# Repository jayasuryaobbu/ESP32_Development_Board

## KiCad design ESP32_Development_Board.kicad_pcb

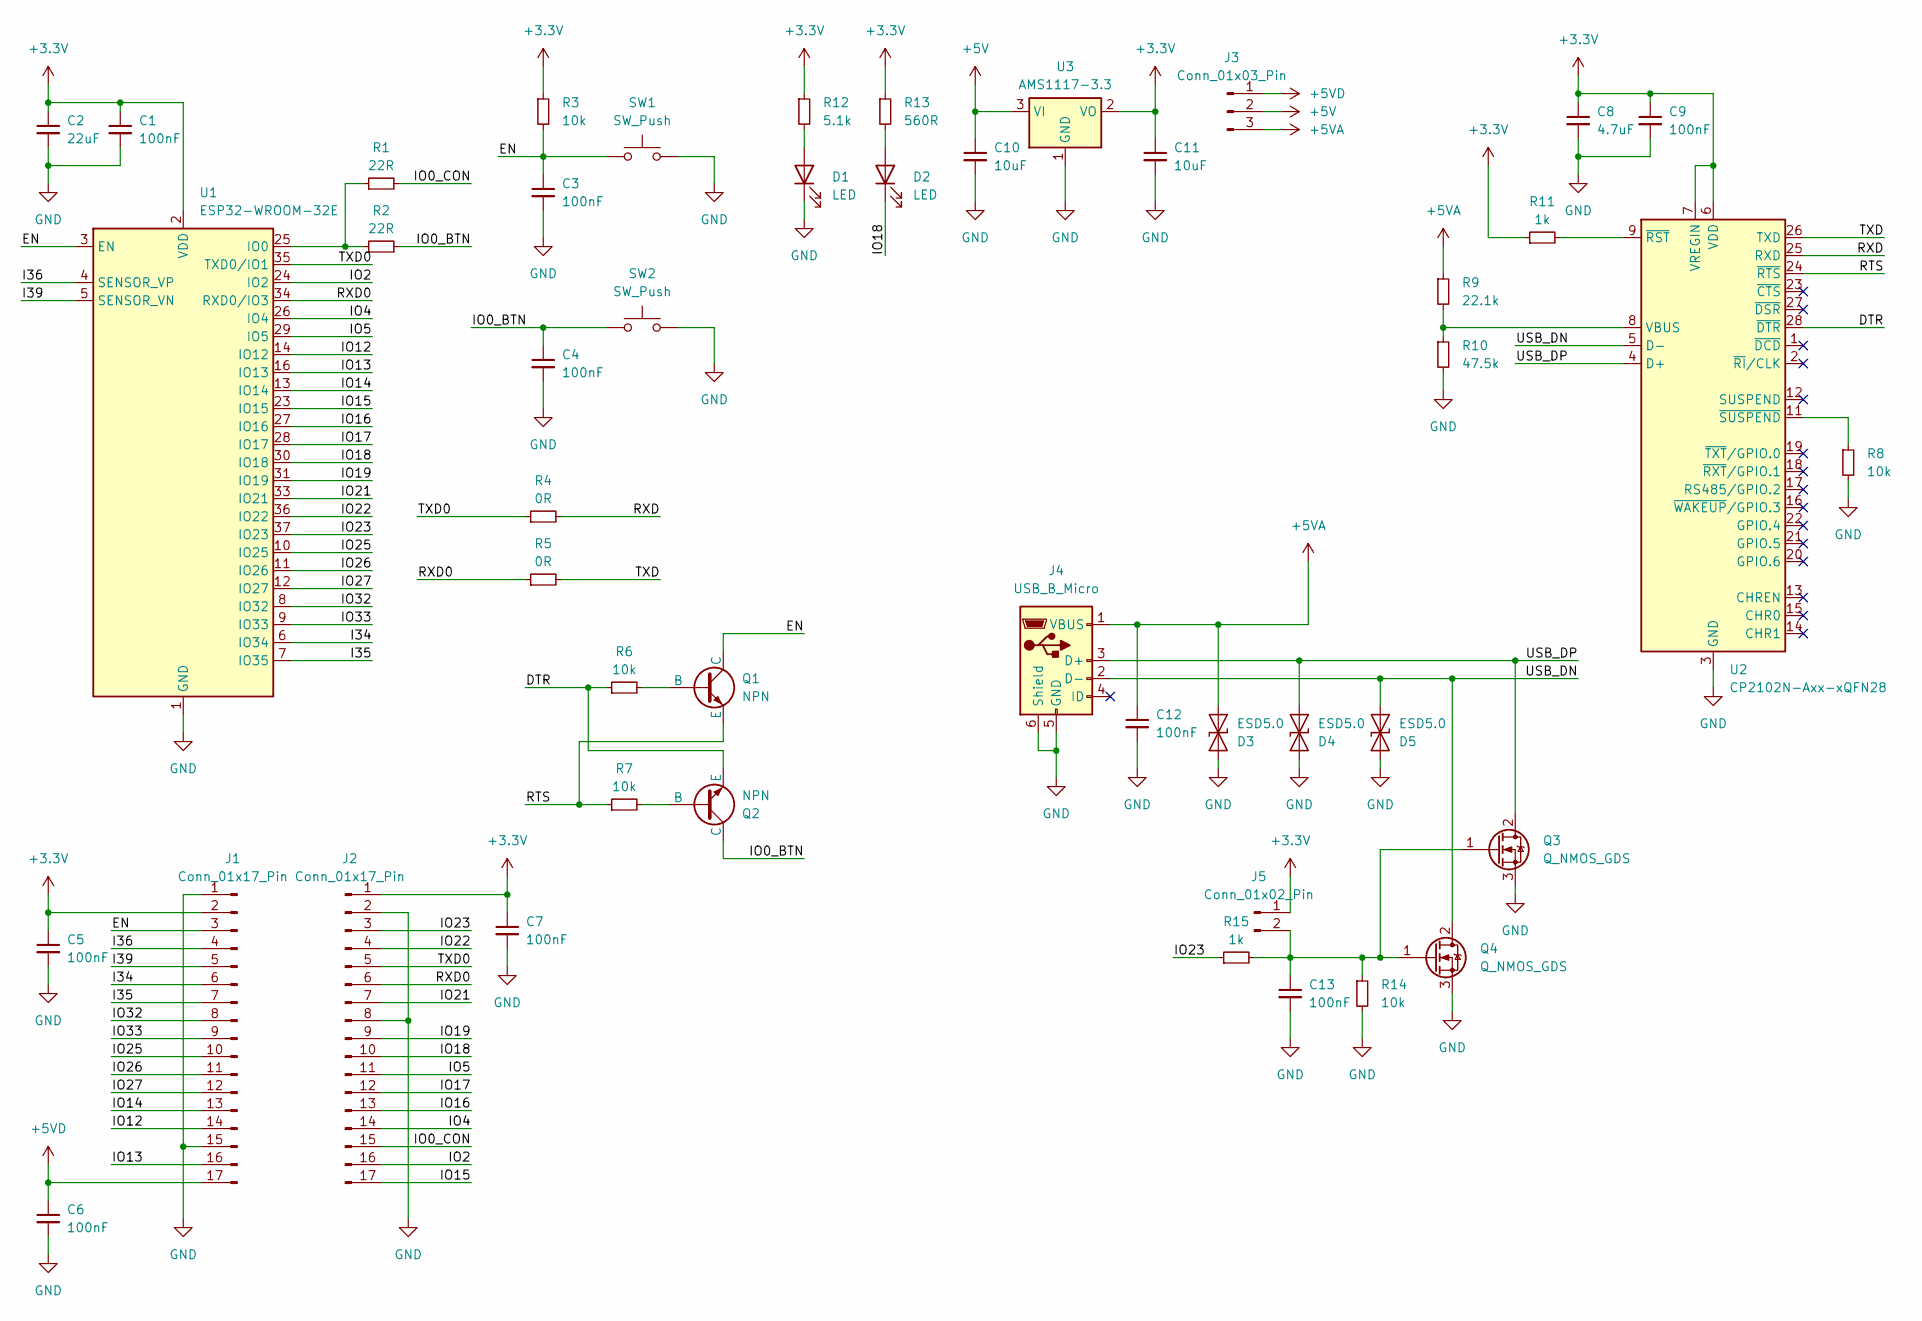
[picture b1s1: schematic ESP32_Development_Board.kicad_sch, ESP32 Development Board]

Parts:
C1, C3, C4, C5, C6, C7, C9, C12, C13: 100nF; C_0402_1005Metric
C2: 22uF; C_0805_2012Metric
C8: 4.7uF; C_0402_1005Metric
C10, C11: 10uF; C_0402_1005Metric
D1, D2: LED; LED_0805_2012Metric
D3, D4, D5: ESD5.0; D_SOD-523
J1, J2: Conn_01x17_Pin; PinHeader_1x17_P2.54mm_Vertical
J3: Conn_01x03_Pin; PinHeader_1x03_P1.27mm_Vertical
J4: USB_B_Micro; USB_Micro-B_Molex-105017-0001
J5: Conn_01x02_Pin; PinHeader_1x02_P1.27mm_Vertical
Q1, Q2: NPN; SOT-23-3
Q3, Q4: Q_NMOS_GDS; SOT-523
R1, R2: 22R; R_0402_1005Metric
R3, R6, R7, R8, R14: 10k; R_0402_1005Metric
R4, R5: 0R; R_0402_1005Metric
R9: 22.1k; R_0402_1005Metric
R10: 47.5k; R_0402_1005Metric
R11, R15: 1k; R_0402_1005Metric
R12: 5.1k; R_0402_1005Metric
R13: 560R; R_0402_1005Metric
SW1, SW2: SW_Push; SW_Push_SPST_NO_Alps_SKRK
U1: ESP32-WROOM-32E
U2: CP2102N-Axx-xQFN28; QFN-28-1EP_5x5mm_P0.5mm_EP3.35x3.35mm
U3: AMS1117-3.3; SOT-89-3

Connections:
+3.3V: C1.1, C2.1, C5.1, C7.1, C8.1, C9.1, C11.1, J1.2, J2.1, J5.1, R3.1, R11.1, R12.1, R13.1, U1.2 (VDD), U2.6 (VDD), U2.7 (VREGIN), U3.2 (VO)
+5V: C10.1, J3.2, U3.3 (VI)
+5VA: C12.1, D3.2 (A2), J3.3, J4.1 (VBUS), R9.1
+5VD: C6.1, J1.17, J3.1
/DTR: Q2.3 (E), R6.1, U2.28 (~DTR)
/EN: C3.1, J1.3, Q1.1 (C), R3.2, SW1.1, U1.3 (EN)
/I34: J1.6, U1.6 (IO34)
/I35: J1.7, U1.7 (IO35)
/I36: J1.4, U1.4 (SENSOR_VP)
/I39: J1.5, U1.5 (SENSOR_VN)
/IO0_BTN: C4.1, Q2.1 (C), R2.2, SW2.1
/IO0_CON: J2.15, R1.2
/IO2: J2.16, U1.24 (IO2)
/IO4: J2.14, U1.26 (IO4)
/IO5: J2.11, U1.29 (IO5)
/IO12: J1.14, U1.14 (IO12)
/IO13: J1.16, U1.16 (IO13)
/IO14: J1.13, U1.13 (IO14)
/IO15: J2.17, U1.23 (IO15)
/IO16: J2.13, U1.27 (IO16)
/IO17: J2.12, U1.28 (IO17)
/IO18: D2.1 (K), J2.10, U1.30 (IO18)
/IO19: J2.9, U1.31 (IO19)
/IO21: J2.7, U1.33 (IO21)
/IO22: J2.4, U1.36 (IO22)
/IO23: J2.3, R15.1, U1.37 (IO23)
/IO25: J1.10, U1.10 (IO25)
/IO26: J1.11, U1.11 (IO26)
/IO27: J1.12, U1.12 (IO27)
/IO32: J1.8, U1.8 (IO32)
/IO33: J1.9, U1.9 (IO33)
/RTS: Q1.3 (E), R7.1, U2.24 (~RTS)
/RXD: R4.2, U2.25 (RXD)
/RXD0: J2.6, R5.1, U1.34 (RXD0/IO3)
/TXD: R5.2, U2.26 (TXD)
/TXD0: J2.5, R4.1, U1.35 (TXD0/IO1)
/USB_DN: D5.2 (A2), J4.2 (D-), Q4.2 (D), U2.5 (D-)
/USB_DP: D4.2 (A2), J4.3 (D+), Q3.2 (D), U2.4 (D+)
GND: C1.2, C2.2, C3.2, C4.2, C5.2, C6.2, C7.2, C8.2, C9.2, C10.2, C11.2, C12.2, C13.2, D1.1 (K), D3.1 (A1), D4.1 (A1), D5.1 (A1), J1.1, J1.15, J2.2, J2.8, J4.5 (GND), J4.6 (Shield), Q3.3 (S), Q4.3 (S), R8.2, R10.2, R14.2, SW1.2, SW2.2, U1.1 (GND), U1.15 (GND), U1.38 (GND), U1.39 (GND), U2.3 (GND), U2.29 (GND), U3.1 (GND)
unnamed: D1.2 (A), R12.2
unnamed: D2.2 (A), R13.2
unnamed: C13.1, J5.2, Q3.1 (G), Q4.1 (G), R14.1, R15.2
unnamed: Q1.2 (B), R6.2
unnamed: Q2.2 (B), R7.2
unnamed: R1.1, R2.1, U1.25 (IO0)
unnamed: R9.2, R10.1, U2.8 (VBUS)
unnamed: R11.2, U2.9 (~RST)
unnamed: R8.1, U2.11 (~SUSPEND)

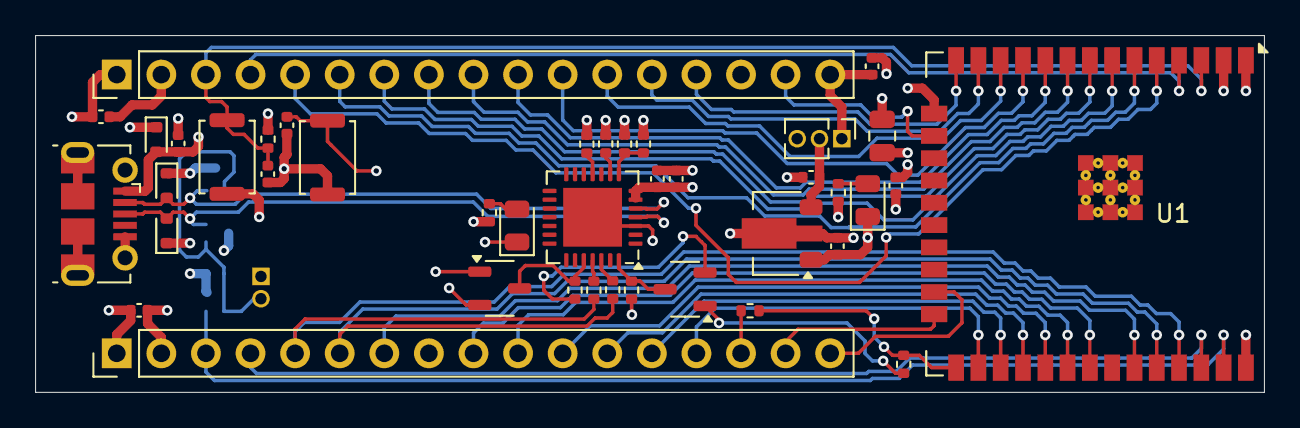
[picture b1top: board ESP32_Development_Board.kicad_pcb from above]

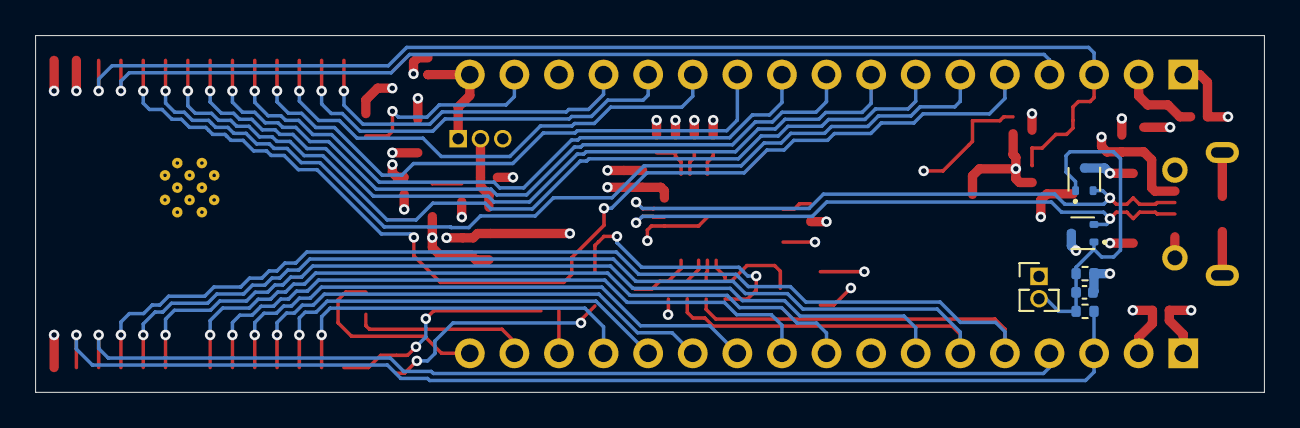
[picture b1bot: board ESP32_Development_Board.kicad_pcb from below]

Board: 4 copper layers, 70.0 x 20.3 mm, 47 parts (6 on the bottom side), 48 nets.

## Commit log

2025-08-11 Moved exsisting private repo project as public repo project
2025-08-11 Added components to PCB
2025-08-11 Placed Components
2025-08-16 Aug 16, 2025
2025-08-17 Scripted auto-commit on change (2025-08-17 13:20:34) by gitwatch.sh
2025-08-17 Scripted auto-commit on change (2025-08-17 13:21:11) by gitwatch.sh
2025-08-17 Commit at 2025-08-17 13:36:59
2025-08-17 Commit at 2025-08-17 17:21:03
2025-08-18 Commit at 2025-08-18 15:00:00
2025-08-18 Commit at 2025-08-18 17:00:00
2025-08-18 Commit at 2025-08-18 18:00:00
2025-08-18 Commit at 2025-08-18 20:04:58
2025-08-20 Commit at 2025-08-20 15:00:01
2025-08-20 Commit at 2025-08-20 16:00:00
2025-08-20 Commit at 2025-08-20 20:00:00
2025-08-20 Commit at 2025-08-20 22:00:00
2025-08-25 Commit at 2025-08-25 19:00:33
2025-08-25 Commit at 2025-08-25 21:00:01
2025-08-28 Commit at 2025-08-28 15:00:00
2025-08-28 Commit at 2025-08-28 21:00:00
